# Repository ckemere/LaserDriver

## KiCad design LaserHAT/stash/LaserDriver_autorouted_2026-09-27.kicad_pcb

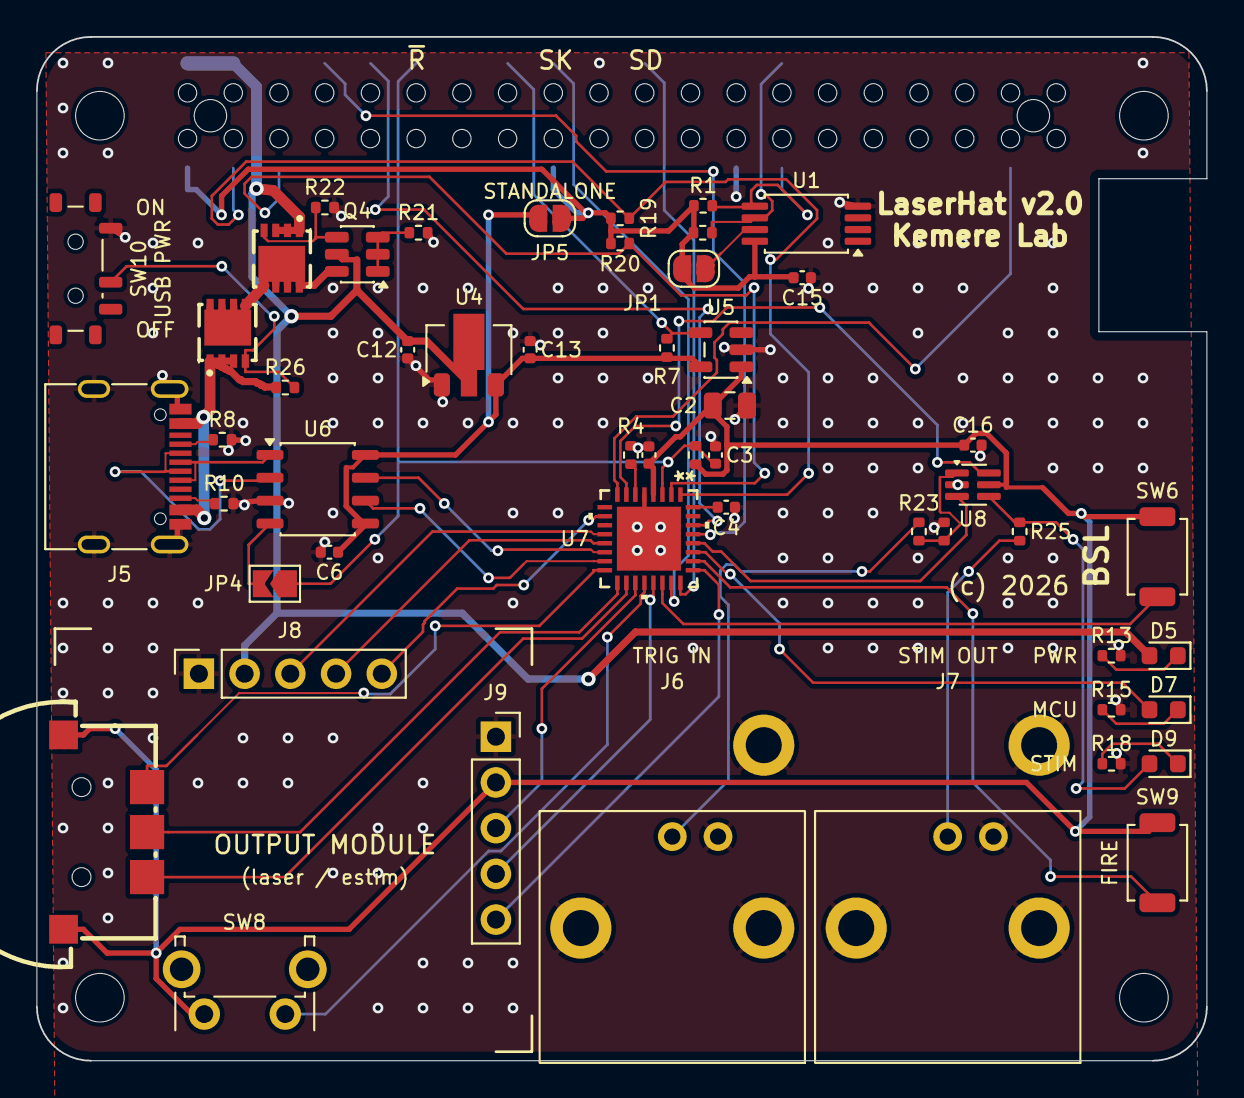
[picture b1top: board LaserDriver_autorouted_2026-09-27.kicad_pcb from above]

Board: 2 copper layers, 65.0 x 56.9 mm, 57 parts (1 on the bottom side), 53 nets.

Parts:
C1, C6, C12, C15, C16: 100nF; C_0402_1005Metric
C2: 10uF; C_0805_2012Metric
C3: 10nF; C_0402_1005Metric
C4: 0.47uF; C_0402_1005Metric
C13: 1uF Ceramic; C_0402_1005Metric
D5: 5V; D_0603_1608Metric
D7: MCU; D_0603_1608Metric
D9: STIM; D_0603_1608Metric
J1: GPIO; Samtec_HLE-120-02-xxx-DV-BE-LC_2x20_P2.54mm_Horizontal
J5: USB_C_Receptacle_USB2.0_16P; USB_C_Receptacle_G-Switch_GT-USB-7010ASV
J6: BNC TRIGGER IN; BNC_Amphenol_031-5540_031-5539_Dual
J7: BNC STIM OUT; BNC_Amphenol_031-5540_031-5539_Dual
J8: DB_POWER_TIMING; PinSocket_1x05_P2.54mm_Vertical
J9: DB_ANALOG; PinSocket_1x05_P2.54mm_Vertical
JP1: ID_WP; SolderJumper-2_P1.3mm_Open_RoundedPad1.0x1.5mm
JP4: RTS_NRST; SolderJumper-2_P1.3mm_Open_TrianglePad1.0x1.5mm
JP5: STANDALONE_3V3; SolderJumper-2_P1.3mm_Open_RoundedPad1.0x1.5mm
MH1, MH2, MH3, MH4: MountingHole_2.7mm_M2.5
Q3, Q5: AP30P30Q; PDFN3333-8_PMOS_GSD
Q4: DMMT5401; SOT-23-6
R1, R2: 3.9k; R_0402_1005Metric
R3: 47k 1%; R_0402_1005Metric
R4: 100k 0.1%; R_0402_1005Metric
R7, R22: 10k; R_0402_1005Metric
R8, R10: 5.1k; R_0402_1005Metric
R13: 3k; R_0402_1005Metric
R15, R18: 2k; R_0402_1005Metric
R19, R20: 4.7k; R_0402_1005Metric
R21: 47k; R_0402_1005Metric
R23: 1k; R_0402_1005Metric
R24, R26: 100k; R_0402_1005Metric
R25: 33; R_0402_1005Metric
SW6: BSL; SW_SPST_TS-1088-xR020
SW7: BL-DT (LCSC C53223909); SW-SMD_BL-DT
SW8: BACK; SW_Tactile_SPST_Angled_PTS645Vx39-2LFS
SW9: FIRE; SW_SPST_TS-1088-xR020
SW10: USB PWR; SW_SPDT_Shouhan_MSK12C02
U1: CAT24C32; TSSOP-8_4.4x3mm_P0.65mm
U4: MCP1700x-330xxMB; SOT-89-3
U5: AP2171W; SOT-23-5
U6: CH340N; JEITA_SOIC-8_3.9x4.9mm_P1.27mm
U7: MSPM0G3507SRHBR; VQFN32_RHB_TEX
U8: 74LVC2G17; SOT-363_SC-70-6

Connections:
+3V3: C6.1, C13.1, JP5.1 (A), R7.1, U4.3 (VO), U5.5 (IN), U6.5 (VCC), U6.8 (V3)
+5V: C12.1, D5.2 (A), J1.2, J1.4, J8.2, Q3.2, Q4.5 (IN), U4.2 (VI)
/BNC + Daughterboard I/O/BNC_IN: J6.1, R23.2
/BNC + Daughterboard I/O/BNC_OUT: J7.1, R25.1
/BNC + Daughterboard I/O/BUF_IN: R23.1, R24.1, U8.1 (S)
/BNC + Daughterboard I/O/BUF_OUT: D9.2 (A), R25.2, U8.4 (S)
/BNC + Daughterboard I/O/STIM_LED_K: D9.1 (K), R18.1
/GPIO18/PCM.CLK: C3.1, J1.12, JP4.1 (A), R3.2, U7.3 (NRST)
/GPIO23: J1.16, R7.2, U5.4 (EN)
/GPIO24: J1.18, U7.23 (PA19/SWDIO)
/GPIO25: J1.22, U7.24 (PA20/SWCLK)
/ID_SCL: J1.28, R2.2, U1.6 (SCL)
/ID_SDA: J1.27, R1.2, U1.5 (SDA)
/MCU_UART_RX: U6.6 (TXD), U7.15 (PA11)
/MCU_UART_TX: U6.7 (RXD), U7.14 (PA10/CLK_OUT)
/MSPM0 Controller/BUTTON1: SW8.1, U7.20 (PA16/A1_1/FCC_IN)
/MSPM0 Controller/BUTTON2: SW7.C, U7.17 (PA13)
/MSPM0 Controller/BUTTON3: SW7.D, U7.18 (PA14/CLK_OUT/A0_12)
/MSPM0 Controller/BUTTON4: SW7.B, U7.16 (PA12/FCC_IN)
/MSPM0 Controller/BUTTON5: SW9.1, U7.26 (PA22/CLK_OUT/A0_7)
/MSPM0 Controller/MSPM0_BSL_INVOKE: SW6.1, U7.22 (PA18/A1_3)
/USB-C UART/CH340_RTS: JP4.2 (B), U6.4 (~RTS)
/USB-C UART/IDEAL_B: Q4.1 (SW), Q4.2 (GND), Q4.3 (FB), R21.1
/USB-C UART/IDEAL_G: Q3.1, Q4.4 (EN), R22.1
/USB-C UART/PWR_EN: Q5.1, R26.2, SW10.2
/USB-C UART/VBUS: J5.A4 (VBUS), J5.A9 (VBUS), J5.B4 (VBUS), J5.B9 (VBUS), Q5.2, R26.1
/USB-C UART/VBUS_SW: Q3.3, Q4.6 (NC), Q5.3
DB_ADC_A: J9.4, U7.21 (PA17/A1_2)
DB_ADC_B: J9.5, U7.25 (PA21/A1_7/VREF-)
DB_DAC: J9.3, U7.19 (PA15/A1_0/DAC_OUT)
DB_GPIO: J8.5, U7.10 (PA6/HFCLK_IN/HFXOUT)
DB_PWM_A: J8.3, U7.12 (PA8)
DB_PWM_B: J8.4, U7.13 (PA9/RTC_OUT/CLK_OUT)
GND: C1.2, C2.2, C3.2, C4.2, C6.2, C12.2, C13.2, C15.2, C16.2, J1.6, J1.9, J1.14, J1.20, J1.25, J1.30, J1.34, J1.39, J5.A1 (GND), J5.A12 (GND), J5.B1 (GND), J5.B12 (GND), J5.S1 (SHIELD), J6.2, J7.2, J8.1, J9.1, R4.2, R8.2, R10.2, R13.2, R15.2, R18.2, R21.2, R22.2, R24.2, SW10.1, U1.4 (GND), U4.1 (GND), U5.2 (GND), U6.3 (GND), U7.5 (VSS), U7.33 (EPAD), U8.2 (G)
I2C_SCL: J1.5, R20.2, U7.2 (PA1)
I2C_SDA: J1.3, R19.2, U7.1 (PA0/FCC_IN)
LED_MCU: D7.2 (A), U7.27 (PA23/VREF+)
MCU_STIM_IN: U7.7 (PA3/COMP1_OUT/LFXIN), U8.6 (D)
MCU_STIM_OUT: U7.28 (PA24/A0_3), U8.3 (D)
MSPM0_3V3: C1.1, C2.1, C16.1, J9.2, R3.1, SW6.2, SW7.A, SW8.2, SW9.2, U5.1 (OUT), U7.4 (VDD), U8.5 (G)
unnamed: D5.1 (K), R13.1
unnamed: D7.1 (K), R15.1
unnamed: J5.A5 (CC1), R8.1
unnamed: J5.B5 (CC2), R10.1
unnamed: JP1.1 (A), U1.7 (WP)
unnamed: J5.A6 (D+), J5.B6 (D+), U6.1 (UD+)
unnamed: J5.A7 (D-), J5.B7 (D-), U6.2 (UD-)
PI_RXD: J1.10, U7.30 (PA26/A0_1)
PI_TRIGGER: J1.37, U7.8 (PA4/LFCLK_IN/LFXOUT)
PI_TXD: J1.8, U7.29 (PA25/A0_2/OPA0_IN1+)
ROSC: R4.1, U7.6 (PA2/ROSC)
RPi +3V3: C15.1, J1.1, J1.17, JP1.2 (B), JP5.2 (B), R1.1, R2.1, R19.1, R20.1, U1.8 (VCC)
VCORE: C4.1, U7.32 (VCORE)

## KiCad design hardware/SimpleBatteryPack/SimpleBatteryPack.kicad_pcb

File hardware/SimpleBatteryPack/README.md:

# SimpleBatteryPack — ±V battery board for the e-stim module, without the charger

Rev A, 2026-10-31.  The BatteryPack (`../BatteryPack`, rev E; archived, tag `archive/pre-glance-cleanup`) with the charging infrastructure cut out.  One 100 × 100 mm
board carries two off-the-shelf 4S hobby packs (LiPo or Li-ion with an XT60 discharge plug, 850–1550 mAh class, about
70–76 × 35 × 30–37 mm) held under it by the case, permanently in series, and gives the e-stim module +V / 0 V / −V
(12.0–16.8 V per rail) on a 4-pin JST-PH.  One toggle does ON / OFF.  **The packs are charged off the board**: unplug the
XT60 and put the pack on an ordinary hobby balance charger.  2-layer (B.Cu = 0V plane; was 4-layer until 2026-11-01, changed for JLC's faster 2-layer turnaround), JLC assembled (toggle, XT60s and the
PH socket through-hole).

## What was cut, and why

| Cut | BatteryPack parts | Consequence |
|---|---|---|
| USB-C PD charger island | J1, U4 CH224A, U18 LDO, Q12 / Q13 VBUS switch, U5 CN3704 buck and its parts (Q6, D7, D8, L1, R25–R27, C3–C11, C22, C23, C28, RT1, R24, R42–R44) | no charging on the board |
| Relays | K1, K2 and their drivers (Q19, Q25, R85–R88, D19, D20) | — |
| Charge controller | U19 STM32F042 with C24–C27, R28, R29, R70–R74, SW2 BOOT, TP1–TP4, the CHG / DONE LEDs D9, D10, D17, D18 + R66–R69; `firmware/` | — |
| Charging interlock | U17 opto + R76 | both rails are still interlocked on 0V reaching the module (Q22, Q26) |
| Balancers + balance sockets | U6–U13 HY2213, Q7–Q10 / Q15–Q18, R31–R38 / R58–R65, C12–C19, J5 / J6 JST-XH | they only bleed a cell above 4.2 V, i.e. while charging; the hobby charger balances.  The balance leads are not plugged in on this board |

Everything else is BatteryPack's, with the same references, values and LCSC codes (`sch_parts.py`), plus one addition,
the −V interlock Q26, and four more M3 holes for the case (H9–H12).  83 parts.

## What is on it

| Block | Parts | Notes |
|---|---|---|
| Pack sockets | J7 (pack A, −V side: GND / 0V), J8 (pack B, +V side: 0V / +BATB), Amass XT60PW-M horizontal (C98732, ext), each set 10 mm back over a notch in the front edge | **0V = pack A's positive = pack B's negative = the output reference, always** |
| Toggle | SW1 MTS-202 DPDT ON-ON (C55159891, ext) | ON / OFF.  Pole 1 (common EN_A): ON → 0V.  Pole 2 (common EN_B): ON → +BATB.  OFF opens both (R40 / R82 hold the enables low) |
| +V chain (pack B) | F1 100 mA PTC, Q1 AO3401A, R1 / R2 100k, Q22 2N7002, R81 1M, U15B (LM393), R53 1M, R82 | +BATB → F1 → +SW → Q1 → +OUT (J3.1).  Q22 turns Q1 on while ENB_G (= EN_B through R81) is high **and its source, J3.4 (CAB), is at 0V**, which only the strap at the module end provides.  U15B pulls ENB_G low below 12.0 V (back above 12.8 V) |
| −V chain (pack A) | F2 100 mA PTC, Q11 AO3400A, R39 / R40 100k, **Q26 AO3401A**, U2B, R11 470k, Q14 + D1 (ON) | GND → F2 → Q11 → −V (J3.3).  Q11's gate is pack A / 2 from EN_AI through R39 / R40; U2B pulls it low below 12.0 V, back on above 12.9 V.  **EN_AI = CAB through Q26**, whose gate is Q20_G (pack A / 2 below 0V while the toggle is ON, 0V when OFF): −V needs the toggle ON *and* CAB at 0V, like +V |
| Gauge rails | Q20 + R77 / R78 + Q21 + R79 / R80 (+G = 0V through Q20); Q23 + R83 / R84 + Q24 (+GB = +BATB through Q23) | follow the toggle |
| Gauges | pack A: U3 CJ431, R3–R10, U1 / U2 LM393, D2–D4 + R13–R15; pack B: U16, R45–R52, U14 / U15, D12–D14 + R55–R57, D11 + R54 ON from +OUT | per pack: green ≥ 15.9 V, green ≥ 15.1 V, yellow ≥ 14.3 V |
| Output | J3 S4B-PH-K-S side-entry (+OUT, 0V, −V, CAB), opening on the right edge, the body's top on the Pi's SE corner (pin 1 lowest) | **pin 4 (CAB) must be strapped to 0V at the module end of the cable**, on its own wire (see below) |
| Mounting | M3 for the case: H1–H4 corners, H9 (48, 25) / H10 (48, 50) on the centre line between the packs, H11 / H12 in the middle of the left / right edges; H5–H8 M2.5 for the Raspberry Pi (58 × 49), 5 mm in from the top edge. No strap slots (removed 2026-11-01: the case holds the packs) | packs under the board in the case, Pi above on ≥ 11 mm standoffs. H9 / H10 are under the Pi: fit the case screws there before the Pi |

Standing draw ON: 10–16 mA (two gauges, ON LEDs) plus the module's ~10 mA; OFF: the cutoff comparators only.

## Operation

- **ON:** both output chains enabled, both gauges lit.  Both rails appear only while CAB is tied to 0V at the module.  A pack below 12.0 V
  drops its rail (the module's fault comparator reports a missing rail); it comes back above 12.8 / 12.9 V.
- **OFF:** both enables open, rails off, gauges dark.
- **Charging:** toggle OFF, unplug the pack's XT60, charge it on a hobby balance charger (4S, 16.8 V), plug it back in.
  Charge both packs to the same state: they are in series, and the lower one cuts its rail first.

Thresholds and values are BatteryPack's (see its README, "Thresholds and values"; the charger lines there do not apply).

## Why both rails are interlocked

BatteryPack interlocked only +V, on the argument that −V without 0V is harmless because nothing in the module conducts
without 0V.  That is a claim about the module, not something this board enforces, so −V now gets the same interlock.
Chain A switches in pack A's negative and is referenced to GND, 16 V below CAB, so CAB cannot simply be Q11's source the
way it is Q22's.  Instead, Q26 (P) passes CAB to R39 while the toggle is ON, using the gauge rail's existing gate node
Q20_G for its drive (−pack A / 2, inside the AO3401A's ±12 V).  The gauges stay on EN_A / EN_B and show without the
module plugged in.

## Board

Built from BatteryPack's board and scripted the same way, then **hand-placed and hand-routed by the user (2026-11-01)**.
The board is now the source: **do not re-run** `place.py`, `orient.py`, `layers2.py`, `j3_bus.py` or `autoroute.py`
(each resets placement or rips copper). The script notes below record how the starting point was made; "Hand layout"
describes the board as it is. Safe on the hand layout: `sync_check.py` / `netcheck.py` (read-only), `pcb_sync.py
--keep-tracks`, `make_fab.py`, and `../tools/track_tidy.py`'s jog steps (skip its HAT-only `header()` step).

- **Netlist:** `tools/pcb_sync.py` (netlist `tools/ref/SimpleBatteryPack.net`).
- **Outline, `tools/place.py`:** 100 × 100 mm with 3 mm corner radii, and two notches 18 × 10 mm (1.5 mm radii) in the
  front edge under the XT60s (2026-11-01). The sockets' faces sit on the notch bottoms (y 90), so a plugged-in pack's
  plug stays inside the outline and its lead comes straight up from the pack underneath. A case round the board and
  packs then has nothing sticking out of the front except the toggle lever. The corner holes and Pi / HAT drawings are
  BatteryPack's (Pi moved 5 mm in from the top edge); BatteryPack's three strap slots are gone, and with them their
  copper keep-outs: the B.Cu 0V plane runs unbroken through the middle of the board.
- **Hand edits:** `place.py` puts everything it draws (outline, keep-outs, its silk) in a group named `place.py` and on a
  re-run removes only that group, so text or graphics added in pcbnew survive it; footprint positions are always reset
  to its table.
- **Placement, `tools/place.py`:**
  - Both gauges and both output chains are in the front strip, on a grid.
  - Pack A's columns run left to right towards its LED column: rail switch, sense divider, CJ431, ladder,
    comparators, then decoupling and the D1 driver.
  - Pack B's gauge mirrors pack A's about x = 50.
  - The ladder and the dividers are literal stacks: 0603s turned pin 1 up, at a 3.2 mm pitch, so each node is the gap
    between two resistors.
  - The LM393s face their inputs to the ladder and their outputs to the LEDs. The two per gauge sit side by side in one
    row (the set-back XT60 fills the space below them, the Pi standoff the space above), each with its decoupling cap
    under its VCC corner.
  - Each chain sits below its gauge, beside its XT60. J3 is on the right edge, its body's top on the Pi's SE corner.
  - SW1 stands between the XT60s with its lever throwing along y; its ON / OFF silk is beside the lever ends, east of
    the switch. (Hand layout: SW1 is turned to −90°, see below.)
  - Rotations that are part of this layout are listed in `LOCKED` and left alone by `tools/orient.py`, which turns the
    rest (62 ratsnest crossings).
- **Layers, `tools/layers2.py`:** 2 copper layers (2026-11-01; the 4-layer version had an In1 0V plane and In2 rail
  pours for the gauges, `tools/layers4.py`, removed). F.Cu carries the parts and most routing; B.Cu is a 0V pour over
  the whole board, the plane. The gauges' rails (GND for gauge A, +GB for gauge B) are tracks.
- **Output bus, `tools/j3_bus.py`:** only +OUT, −V and CAB have to reach J3. They are pre-routed by hand, locked, on
  B.Cu along the board's edges, so they do not cut the 0V plane through the middle. The route runs down the right edge, then west
  along the bottom of the board below the XT60 and toggle pins (y 87.8 / 89.2), to the chains. The chain FETs' rotations
  are locked so the bus ends stay on their pads. The strip of B.Cu south of the bus is left unpoured (island removal).
- **Routing:** `tools/autoroute.py` (Freerouting) routes everything but 0V, which it is kept off (left one pin in the
  DSN). `tools/plane_vias.py 0V --apply` then drops a via to the B.Cu plane by each 0V SMD pad (THT pads are in the
  pour). A last `ROUTE_0V=1 tools/autoroute.py --continue` routes 0V as tracks for any pad whose via lands on a piece of
  plane the B.Cu tracks have cut off; check the fill is one piece afterwards (2026-11-01: one piece, 7948 mm²).
  `plane_vias.py` also takes `--pad REF.PAD` for a pad group that is tied by tracks but has no via.

### Hand layout (2026-11-01, the board as built)

- **Toggle SW1** is at −90°: pins 1 / 4 (0V, +BATB) at the back (y 74.8), the unused throws 3 / 6 at the front
  (y 84.2). A bat-handle toggle closes the end **opposite** the lever, so the lever pushed **toward the front (toward
  3 / 6) is ON** and toward the back is OFF. The silk says so: ON at the front end (y 84.25), OFF at the back (y 74.25).
- **Gauge A** (pack A, referenced to GND = pack A −): GND is hand-routed as 0.8 mm tracks, mostly on B.Cu through the
  0V plane. An F.Cu GND pour was tried and dropped: its edge came within an M3 washer's reach of H10, with the 0V plane
  on the other face, so a metal screw there could short pack A. Nearest GND copper to H10 is now 3.1 mm from the hole.
- **Gauge B** (pack B, referenced to 0V): an F.Cu 0V pour (x 64–83, y 44–76) under it, stitched to the B.Cu plane.
- **Output bus:** −V still follows the locked `j3_bus.py` route (right edge, then west along y 87.8). +OUT and CAB are
  hand-routed: CAB on B.Cu from J3.4 diagonally to y 45.5, west across the board to x 26.5, then down x 15 to Q26; a
  branch to Q22. The B.Cu 0V plane stays one piece around both ends of that run.
- **Pin rings:** `tht_to_pour` in `SimpleBatteryPack.kicad_dru` keeps 1 mm of bare board between every through-hole
  pin and a pour of another net. The XT60 and toggle pins carry big solder fillets, and a bridge from J7.1 (GND),
  J8.2 or SW1.4 (+BATB) to the 0V plane is a dead pack short.
- **Battery spacing:** pack A − (GND) to pack B + (+BATB) is ≥ 1 mm everywhere on both layers; within one pack the
  closest copper is 0.3 mm (track to pour, under solder mask).
- **Silk:** gauge labels (A, B, 80 / 50 / 20 %, ON) are 1.0 mm / 0.15 mm stroke, all front text at 180° (read with the
  notches away from you). "OUT" by J3 and "CK SDG" on the back are still 0.8 mm (below JLC's 1.0 mm). The back pack
  outlines start at y 11, clear of the H7 / H8 standoffs.
- **The owl (G1):** decorative copper with no net (its 0V connection was removed in the schematic), so it adds no
  unconnected items.

Result 2026-11-01 19:48 (hand layout): DRC 0 violations, 0 warnings, 0 unconnected, 0 schematic-parity issues;
`sync_check` 0 differences (84 parts); B.Cu 0V plane one piece, F.Cu 0V pour 9 pieces, all connected.

## Assembly notes and first-article checks

- **Toggle lever direction:** lever toward the "ON" silk (the front, pins 3 / 6) should close common 2 → 1 and 5 → 4.
  Check one MTS-202 with a meter before assembly (lever toward pins 1 / 4: 2–1 open, 2–3 closed). If it is the other
  way round, swap the ON / OFF texts on SW1 in the board (they are board-level edits now, not `make_footprints.py`'s).
- **0V interlock (both rails):** run CAB (J3.4) up the cable as its own wire and tie it to 0V **at the module**, not in
  the PH plug at this board (on the module's next rev, strap its socket's pins 2 and 4).  Then Q22 and Q26 conduct only
  while the 0V wire really reaches the module: a broken 0V wire, a cracked joint or an unseated module end turns both
  rails off, which is the failure that killed the module twice.  A strap in the battery-end plug works, but it only
  proves that plug is seated.  Without any strap neither rail comes on.
- **XT60 polarity:** the footprint puts − at pad 1 (the end with the two bevelled corners) and + at the square-cornered
  end, which is how hobby packs are wired (red to the flat side).  Check a pack's plug with a meter against the silk + / −
  before the first pack goes in.
- **JLC rotation:** check the SOT-23s, SOICs and LEDs in JLC's DFM preview (same correction table as BatteryPack).
- Extended parts: toggle, XT60 sockets, PTCs, PH-4 header.  Everything else is basic.

## Checks before fab

**The schematic is hand-edited since 2026-11-01** (gauge B's comparator units reassigned — U14 A/B = TH50B/TH80B,
U15 A = cutoff, U15 B = TH20B — and the owl taken off 0V), so `gen_schematic.py` / `sch_parts.py` are stale: **do not
re-run `gen_schematic.py`**, it would undo those edits, and `tools/netcheck.py` (which checks against `sch_parts.py`)
now reports the gauge-B nets as a mismatch.  Checks: ERC (0) → F8 / `tools/pcb_sync.py --keep-tracks` only if nets or
footprints changed → `kicad-cli pcb drc` (0 / 0 / 0, parity included) → `../tools/sync_check.py` → `python
tools/lcsc_check.py` → `python tools/make_fab.py` (writes `../fab/SimpleBatteryPack/`; not run yet).

Shared with BatteryPack and copied here: `battpack.pretty` / `battpack.3dshapes` / `battpack.kicad_sym` (some footprints
in them, such as the relay and opto, are unused), `sch_engine.py`, `sch_symbols.py` and the board tools.  Symbol UUIDs are
derived from the references, so they are the same as BatteryPack's for the parts the two boards share.

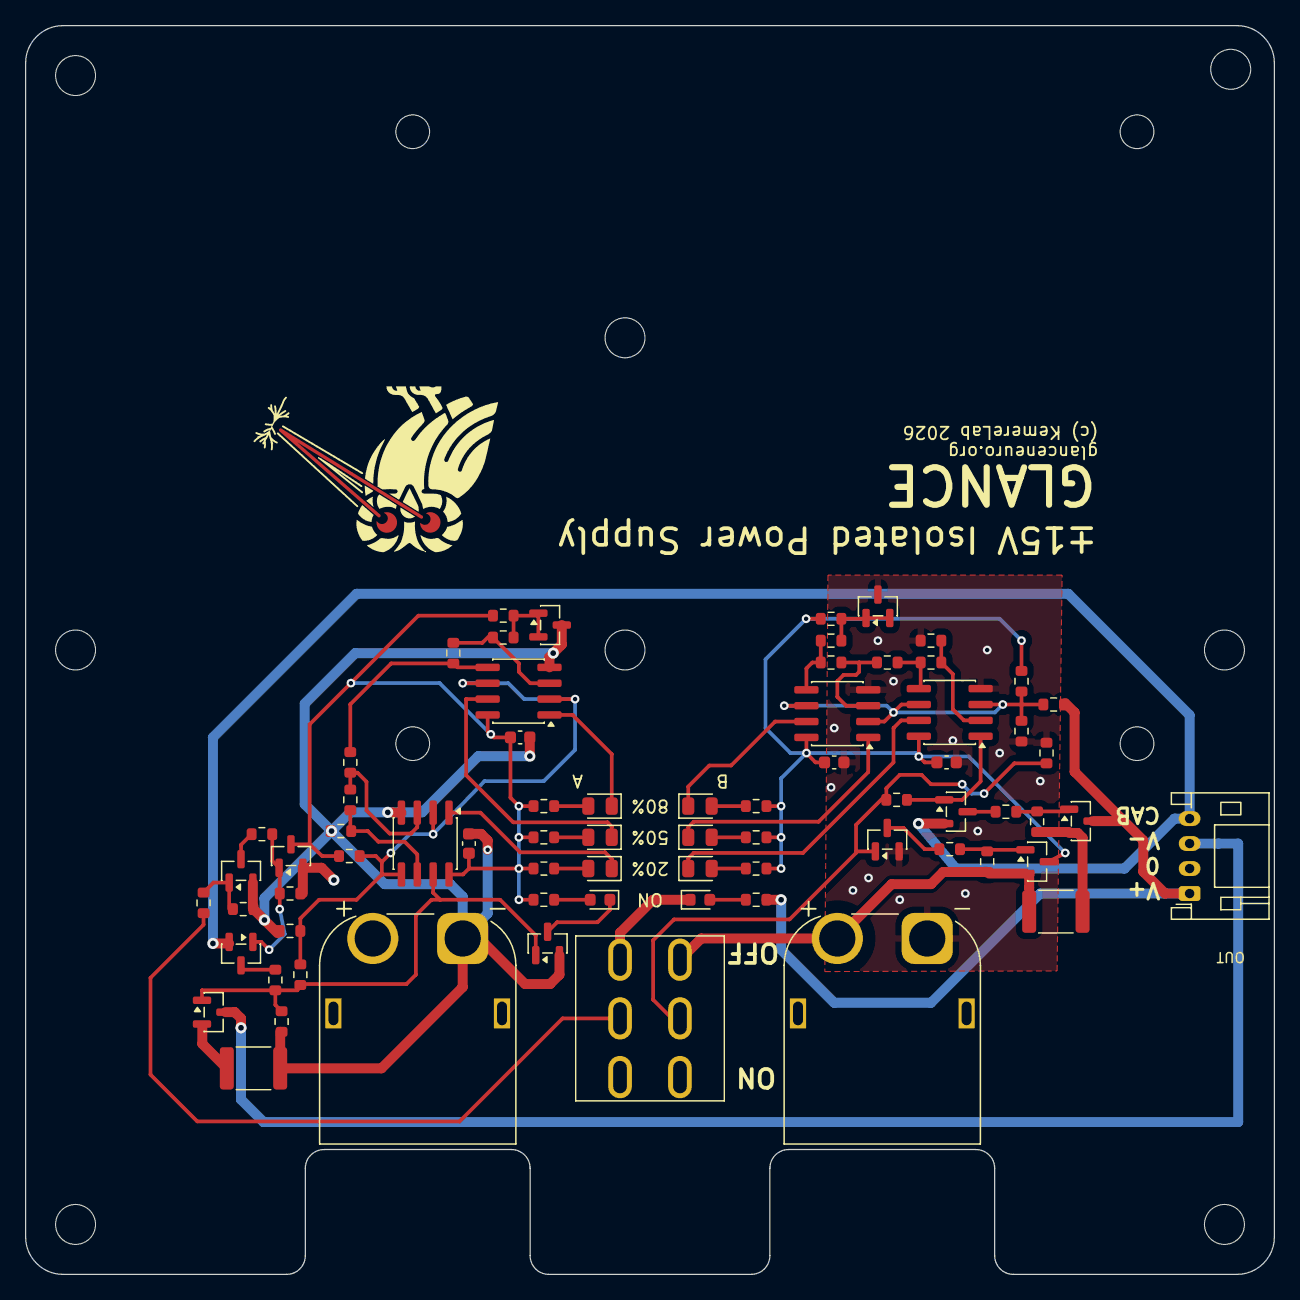
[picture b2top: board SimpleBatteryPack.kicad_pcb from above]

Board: 2 copper layers, 100.0 x 100.0 mm, 84 parts (0 on the bottom side), 49 nets.

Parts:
C1, C2, C20, C21: 100n; C_0603_1608Metric
D1, D11: KT-0603R; LED_0603_1608Metric
D2, D12: KT-0805Y; LED_0805_2012Metric
D3, D4, D13, D14: KT-0805G; LED_0805_2012Metric
F1, F2: MF-MSMF010-2; Fuse_1812_4532Metric
G1: OwlLogo; OwlLogo_Eyes_14mm_R
H1, H2, H3, H4, H9, H10, H11, H12: M3; MountingHole_3.2mm_M3
H5, H6, H7, H8: M2.5; MountingHole_2.7mm_M2.5
J3: S4B-PH-K-S(LF)(SN); JST_PH_S4B-PH-K_1x04_P2.00mm_Horizontal
J7, J8: XT60PW-M
Q1, Q20, Q23, Q26: AO3401A; SOT-23
Q11, Q14: AO3400A; SOT-23
Q21, Q22, Q24: 2N7002; SOT-23
R1, R2, R39, R40, R77, R78, R79, R80, R83, R84: 100k; R_0603_1608Metric
R3, R45: 6.8k; R_0603_1608Metric
R4, R7, R46, R49: 6.2k; R_0603_1608Metric
R5, R6, R47, R48: 2k; R_0603_1608Metric
R8, R50: 30k; R_0603_1608Metric
R9, R51: 68k; R_0603_1608Metric
R10, R52: 10k; R_0603_1608Metric
R11: 470k; R_0603_1608Metric
R12, R13, R54, R55: 13k; R_0603_1608Metric
R14, R15, R56, R57: 12k; R_0603_1608Metric
R53, R81, R82: 1M; R_0603_1608Metric
SW1: CAX-MTS202B2-BB-20.5JL; SW_MTS-202
U1, U2, U14, U15: LM393DR2G; SOIC-8_3.9x4.9mm_P1.27mm
U3, U16: CJ431; SOT-23

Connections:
0V: C20.2, C21.2, D11.1 (K), J3.2, J7.2, J8.1, Q20.2 (S), Q24.2 (S), R50.2, R52.2, R77.1, R82.2, SW1.1 (A1), U14.4 (V-), U15.4 (V-), U16.3 (A)
+BATB: F1.1, J8.2, Q23.2 (S), R83.1, SW1.4 (A2)
+G: C1.1, C2.1, Q20.3 (D), R3.1, R9.1, R12.1, R13.1, R14.1, R15.1, U1.8 (V+), U2.8 (V+)
+GB: C20.1, C21.1, Q23.3 (D), R45.1, R51.1, R55.1, R56.1, R57.1, U14.8 (V+), U15.8 (V+)
+OUT: J3.1, Q1.3 (D), R53.1, R54.1
+SW: F1.2, Q1.2 (S), R1.1
/-V: J3.3, Q11.3 (D)
/CAB: J3.4, Q22.2 (S), Q26.2 (S)
/D1_K: D1.1 (K), Q14.3 (D)
/ENB_G: Q22.1 (G), R81.2, U15.1
/EN_A: R79.1, SW1.2 (C1)
/EN_AI: Q26.3 (D), R39.1
/EN_B: Q24.1 (G), R81.1, R82.1, SW1.5 (C2)
/GNDF: F2.2, Q11.2 (S)
/Q1_G: Q1.1 (G), R1.2, R2.1
/Q11_G: Q11.1 (G), Q14.1 (G), R11.1, R39.2, R40.1, U2.7
/Q20_G: Q20.1 (G), Q26.1 (G), R77.2, R78.1
/Q21_D: Q21.3 (D), R78.2
/Q21_G: Q21.1 (G), R79.2, R80.1
/Q22_D: Q22.3 (D), R2.2
/Q23_G: Q23.1 (G), R83.2, R84.1
/Q24_D: Q24.3 (D), R84.2
/TH20: R6.2, R7.1, U2.3 (+)
/TH20B: R48.2, R49.1, U15.5 (+)
/TH50: R5.2, R6.1, U1.5 (+)
/TH50B: R47.2, R48.1, U14.3 (+)
/TH80: R4.2, R5.1, U1.3 (+)
/TH80B: R46.2, R47.1, U14.5 (+)
/THCUT: R7.2, R8.1, U2.6 (-)
/THCUTB: R49.2, R50.1, U15.2 (-)
/VREF: R3.2, R4.1, U3.1 (REF), U3.2 (K)
/VREFB: R45.2, R46.1, U16.1 (REF), U16.2 (K)
/VS: R9.2, R10.1, R11.2, U1.2 (-), U1.6 (-), U2.2 (-), U2.5 (+)
/VSB: R51.2, R52.1, R53.2, U14.2 (-), U14.6 (-), U15.3 (+), U15.6 (-)
GND: C1.2, C2.2, F2.1, J7.1, Q14.2 (S), Q21.2 (S), R8.2, R10.2, R40.2, R80.2, U1.4 (V-), U2.4 (V-), U3.3 (A)
unnamed: D1.2 (A), R12.2
unnamed: D2.2 (A), R13.2
unnamed: D2.1 (K), U2.1
unnamed: D3.2 (A), R14.2
unnamed: D3.1 (K), U1.7
unnamed: D4.2 (A), R15.2
unnamed: D4.1 (K), U1.1
unnamed: D11.2 (A), R54.2
unnamed: D12.2 (A), R55.2
unnamed: D12.1 (K), U15.7
unnamed: D13.2 (A), R56.2
unnamed: D13.1 (K), U14.1
unnamed: D14.2 (A), R57.2
unnamed: D14.1 (K), U14.7

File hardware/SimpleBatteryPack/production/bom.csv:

Designator,Footprint,Quantity,Value,LCSC Part #
"C1, C2, C20, C21",0603,4,100n,C14663
"D1, D11",0603,2,KT-0603R,C2286
"D12, D2",0805,2,KT-0805Y,C2296
"D13, D14, D3, D4",0805,4,KT-0805G,C2297
"F1, F2",1812,2,MF-MSMF010-2,C12430
J3,JST_PH_S4B-PH-K_1x04_P2.00mm_Horizontal,1,S4B-PH-K-S(LF)(SN),C157926
"J7, J8",XT60PW-M,2,XT60PW-M,C98732
"Q1, Q20, Q23, Q26",SOT-23,4,AO3401A,C15127
"Q11, Q14",SOT-23,2,AO3400A,C20917
"Q21, Q22, Q24",SOT-23,3,2N7002,C8545
"R1, R2, R39, R40, R77, R78, R79, R80, R83, R84",0603,10,100k,C25803
"R10, R52",0603,2,10k,C25804
R11,0603,1,470k,C23178
"R12, R13, R54, R55",0603,4,13k,C22797
"R14, R15, R56, R57",0603,4,12k,C22790
"R3, R45",0603,2,6.8k,C23212
"R4, R46, R49, R7",0603,4,6.2k,C4260
"R47, R48, R5, R6",0603,4,2k,C22975
"R50, R8",0603,2,30k,C22984
"R51, R9",0603,2,68k,C23231
"R53, R81, R82",0603,3,1M,C22935
SW1,SW_MTS-202,1,CAX-MTS202B2-BB-20.5JL,C55159891
"U1, U14, U15, U2",SOIC-8_3.9x4.9mm_P1.27mm,4,LM393DR2G,C7955
"U16, U3",SOT-23,2,CJ431,C3113

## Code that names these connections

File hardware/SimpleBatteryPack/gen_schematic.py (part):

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W("SW1.4", (30, 61), (30, 66)); pwr_at("+BATB", 30, 66, (0, 1))                                 # ON: EN_B = +BATB
put("R82", 12, 72)                                        # EN_B pull-down
NET("R82.1"); PWR("R82.2")
# chain B (0V domain): +BATB -> F1 -> +SW -> Q1 -> +OUT, enabled by Q22 (gate ENB_G, source = the plug's pin 4)
put("F1", 46, 58, rot=90)
PWR("F1.1", length=2.54)
e = PWR("F1.2", length=2.54); FLAG(e, up=(1, 0))           # +SW
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put("U2", 80, 94, unit=2)                                 # pack A cutoff comparator (+ = VS, - = THCUT: output low = off)
NET("U2.5"); NET("U2.6"); NET("U2.7")
text("SW1 ON: pole 1 puts EN_A at 0V (= pack A positive), pole 2 puts EN_B at +BATB; OFF opens both (R40 / R82 hold them low).  Chain B: Q22 (2N7002) conducts when ENB_G is high", 7, 103)
text("and its source, J3.4 (CAB), is at 0V, i.e. the strap at the module end ties pin 4 to pin 2: then R1 / R2 give Q1 Vgs = -Vsw/2 and +V is live.  ENB_G = EN_B through R81 1M, pulled to 0V by", 7, 105)
text("U15B below 12.0 V (back above 12.8 V: R53 from +OUT).  Chain A: Q11 (N, in pack A's negative) gets Vgs = pack A / 2 from R39 / R40 off EN_AI = CAB through Q26,", 7, 107)
text("which conducts while the toggle is ON (its gate is Q20_G, pack A / 2 below 0V); U2B pulls Q11's gate low below 12.0 V (R11 470k: back on at 12.9 V).  So both rails need", 7, 109)
text("the toggle ON and 0V present at the module.  Gauge rails (box 2B) follow EN_A / EN_B, not the interlock: both gauges show whenever the toggle is ON.", 7, 111)
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    put(h, 170 + 6 * i, 133, ref_at=(0, -3.81), val_at=(0, 3.81))
text("H1-H4 corners, H9 / H10 between the packs, H11 / H12 mid-edge: M3, the case.  H5-H8 M2.5: a Raspberry Pi above.", 159, 137)
text("The case holds the packs under the board; their XT60 leads come up through the front notches to J7 / J8.", 159, 139)
text("J3 pin 4 (CAB) is tied to 0V at the module end of the cable, on its own wire: both rails are enabled only", 159, 141)
text("while 0V really reaches the module.  Toggle ON powers the module and the gauges; OFF leaves only", 159, 143)
text("the cutoff comparators' few uA on the packs.", 159, 145)
text("-V floats whenever pack A is off (OFF, under-voltage), +V whenever pack B is or the plug is out:", 159, 147)
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

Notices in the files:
LaserHAT/stash/LaserDriver_autorouted_2026-09-27.kicad_pcb:
(c) 2026
